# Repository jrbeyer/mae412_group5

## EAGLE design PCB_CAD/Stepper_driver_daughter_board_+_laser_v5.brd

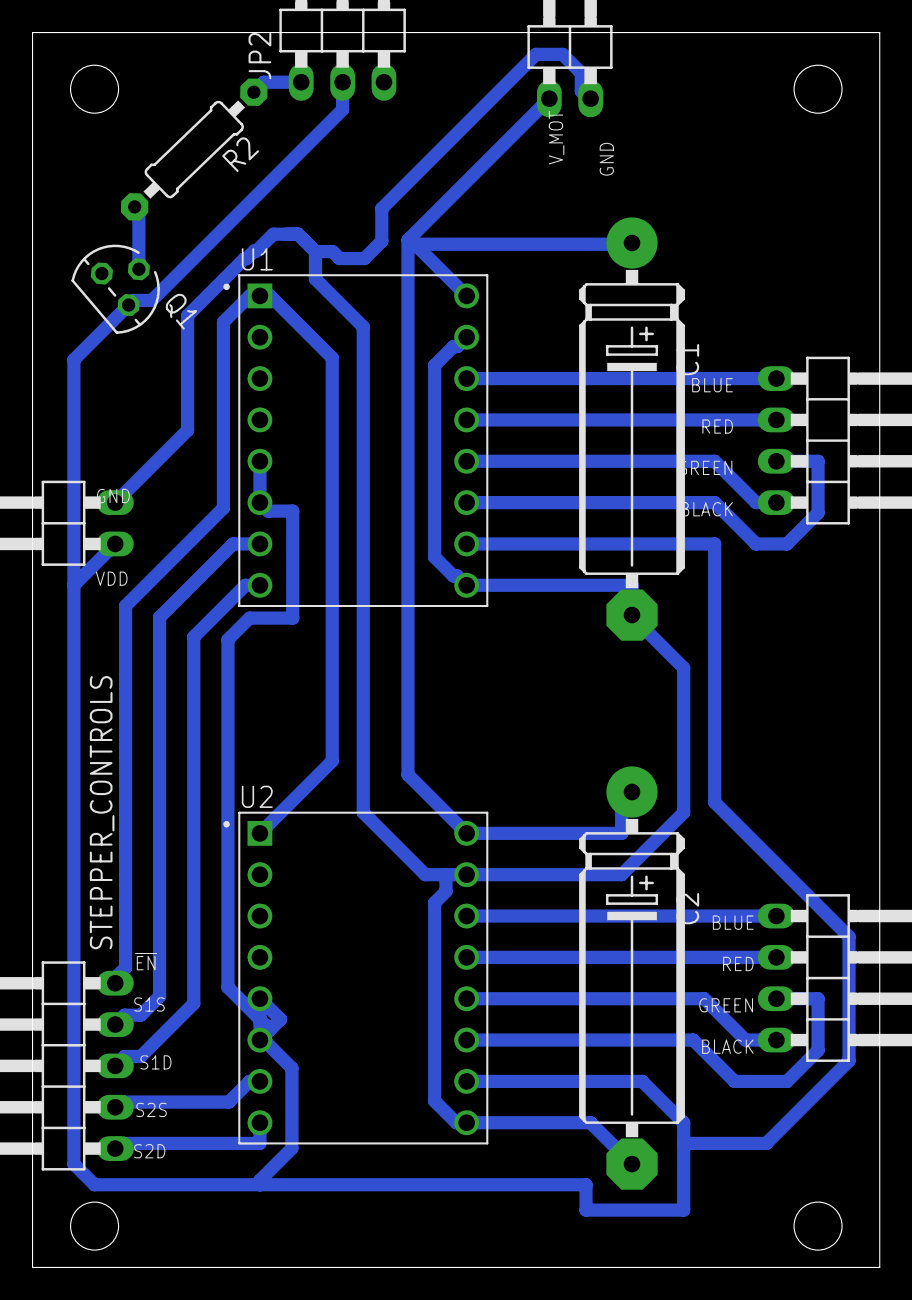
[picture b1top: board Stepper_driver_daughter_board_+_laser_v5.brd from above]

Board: 2 copper layers, 52.0 x 75.9 mm, 12 parts (0 on the bottom side), 18 nets.

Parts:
C1, C2: 100u; E22-6
JP2: PINHD-1X3/90; 1X03/90
Q1: NPN; TO92
R2: 2.4k; 0207/10
STEPPER1_OUT, STEPPER2_OUT: PINHD-1X4/90; 1X04/90
STEPPER_CONTROLS: PINHD-1X5/90; 1X05/90
U1, U2: A4988_STEPPER_MOTOR_DRIVER_CARRIER; MODULE_A4988_STEPPER_MOTOR_DRIVER_CARRIER
V_DD: PINHD-1X2/90; 1X02/90
V_MOT: PINHD-1X2/90; 1X02/90

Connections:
!ENABLE: STEPPER_CONTROLS.5, U1.1, U2.1
BASE: Q1.2, R2.2
GND: C1.-, C2.-, JP2.3, Q1.1, U1.9, U1.15, U2.9, U2.15, V_DD.2, V_MOT.2
LASER_SWITCH: JP2.1, R2.1
STEPPER1_BLACK: STEPPER1_OUT.4, U1.12
STEPPER1_BLUE: STEPPER1_OUT.1, U1.14
STEPPER1_DIR: STEPPER_CONTROLS.3, U1.8
STEPPER1_GREEN: STEPPER1_OUT.3, U1.11
STEPPER1_RED: STEPPER1_OUT.2, U1.13
STEPPER1_STEP: STEPPER_CONTROLS.4, U1.7
STEPPER2_BLACK: STEPPER2_OUT.4, U2.12
STEPPER2_BLUE: STEPPER2_OUT.1, U2.14
STEPPER2_DIR: STEPPER_CONTROLS.1, U2.8
STEPPER2_GREEN: STEPPER2_OUT.3, U2.11
STEPPER2_RED: STEPPER2_OUT.2, U2.13
STEPPER2_STEP: STEPPER_CONTROLS.2, U2.7
VDD: JP2.2, Q1.3, U1.5, U1.6, U1.10, U2.5, U2.6, U2.10, V_DD.1
VMOT: C1.+, C2.+, U1.16, U2.16, V_MOT.1

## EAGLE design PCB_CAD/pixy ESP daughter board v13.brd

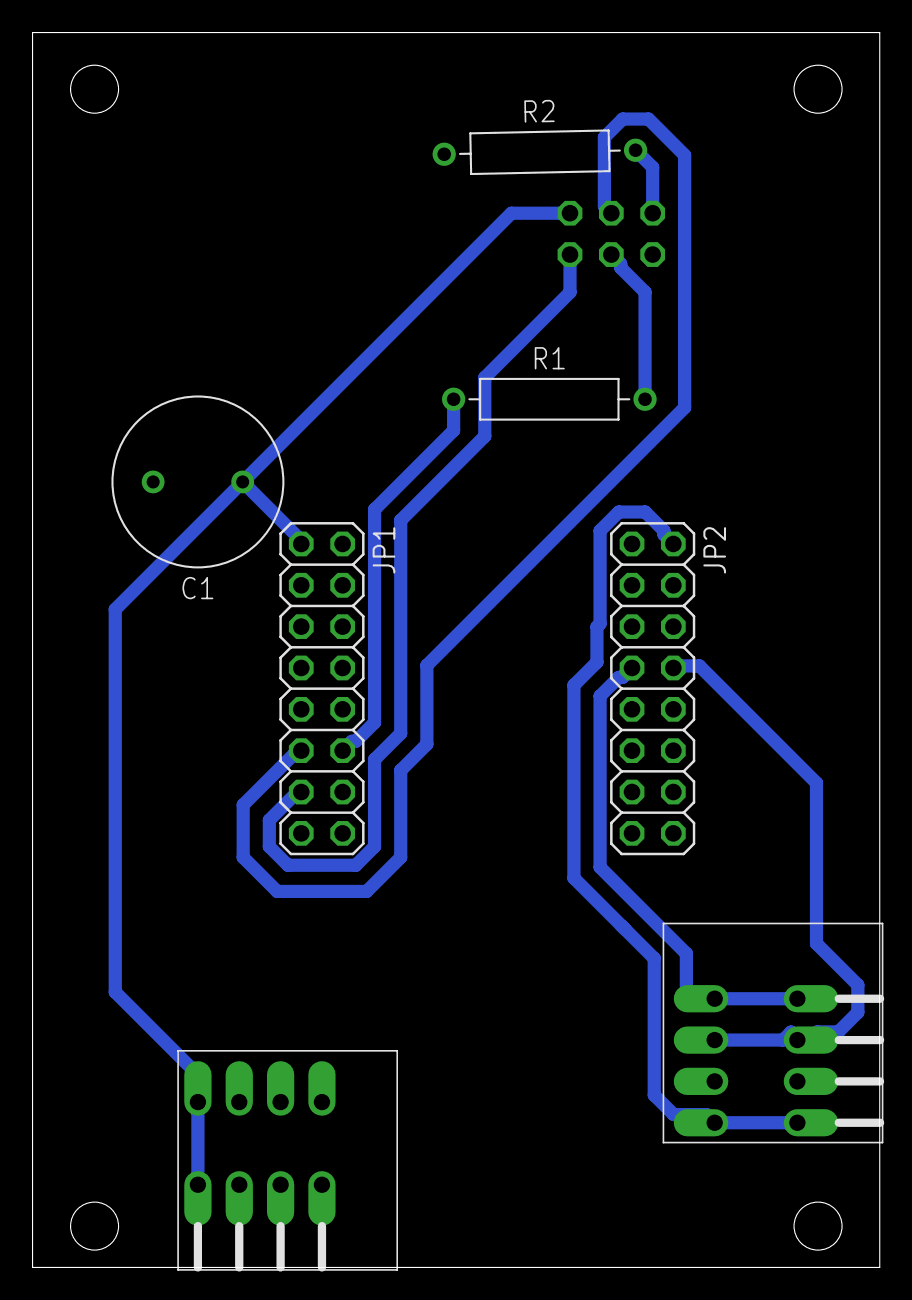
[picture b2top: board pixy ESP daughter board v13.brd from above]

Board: 2 copper layers, 52.0 x 75.9 mm, 8 parts (1 on the bottom side), 10 nets.

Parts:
C1: 10u; CAPRD550W60D1025H1250B
JP1, JP2: PINHD-2X8; 2X08
JP4: PINHD-2X3; 2X03
POWER_IN: TE_CONN_1-2834016-4; 1-2834016-4
R1, R2: 0; RESAD1176W63L850D250B
VL53L0X1: TE_CONN_1-2834016-4; 1-2834016-4

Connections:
3V3: JP2.2, VL53L0X1.P$1, VL53L0X1.P$2
35: JP1.11, JP4.3
36: JP1.12, R1.1
36_PIXY: JP4.4, R1.2
37: JP1.13, JP4.2
GND: C1.2, JP1.3, JP1.4, POWER_IN.P$3, POWER_IN.P$4, POWER_IN.P$5, POWER_IN.P$6, POWER_IN.P$7, POWER_IN.P$8, R2.1, VL53L0X1.P$3, VL53L0X1.P$4
GND_PIXY: JP4.5, R2.2
SCL: JP2.8, VL53L0X1.P$5, VL53L0X1.P$6
SDA: JP2.7, VL53L0X1.P$7, VL53L0X1.P$8
VDD: C1.1, JP1.1, JP4.1, POWER_IN.P$1, POWER_IN.P$2

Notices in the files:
parts and their libraries:
1-2834016-4: Licensing: Creative Commons ShareAlike 4.0 International - https://creativecommons.org/licenses/by-sa/4.0
